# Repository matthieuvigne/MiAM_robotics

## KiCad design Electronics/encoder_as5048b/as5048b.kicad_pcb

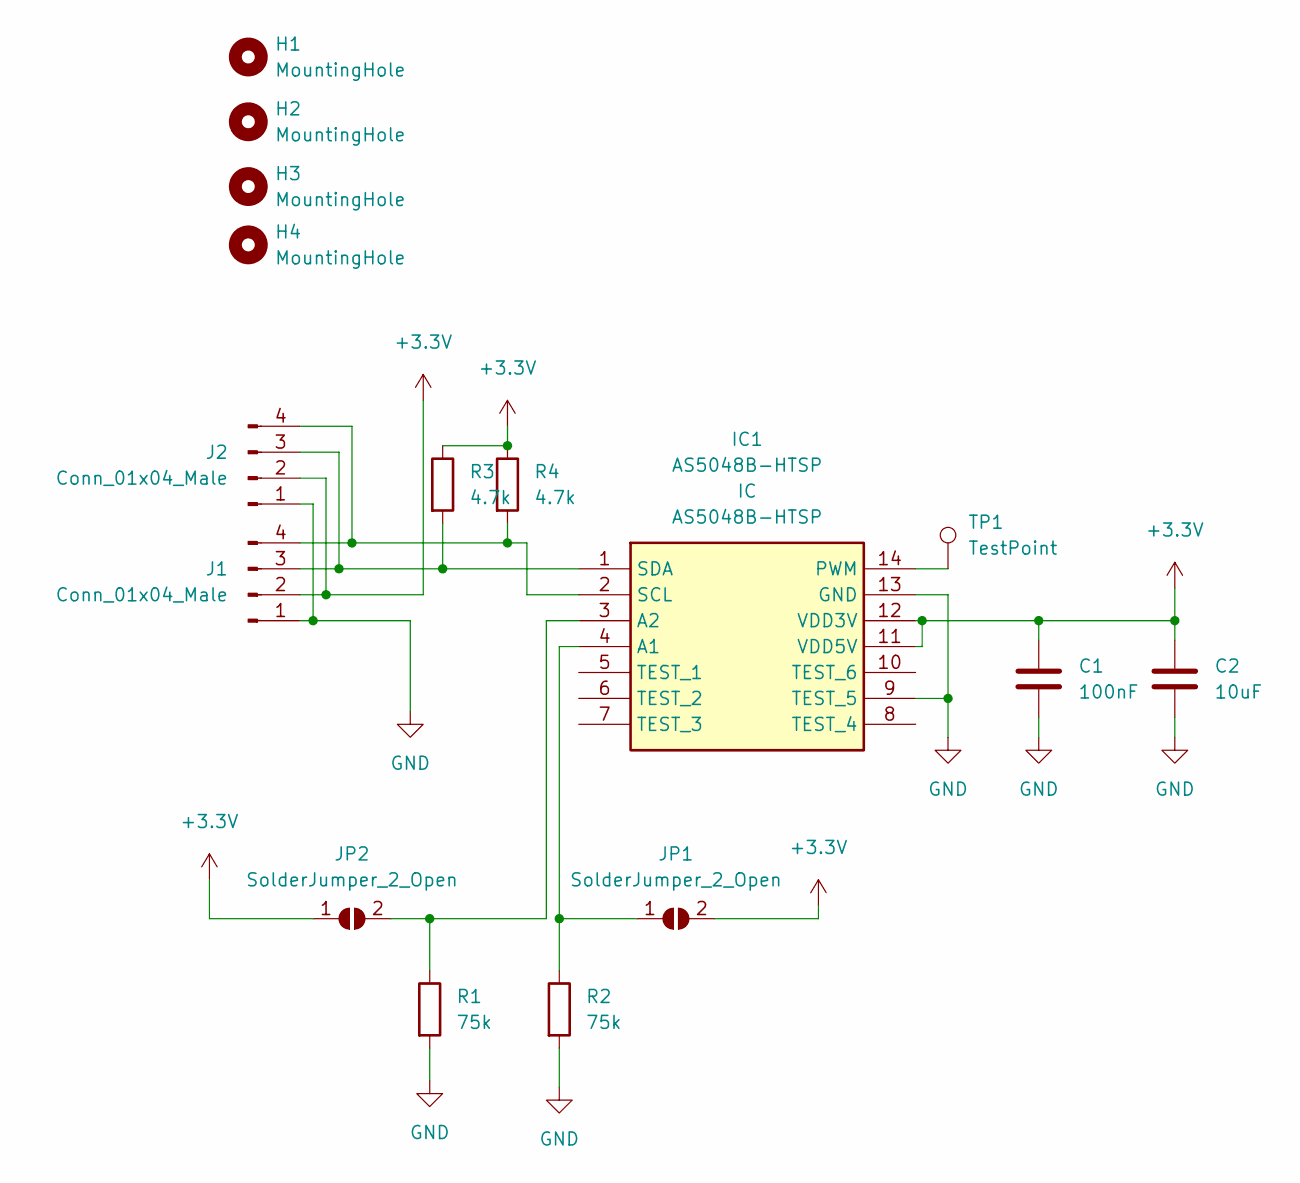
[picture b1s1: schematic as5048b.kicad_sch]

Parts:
C1: 100nF; C_0402_1005Metric_Pad0.74x0.62mm_HandSolder
C2: 10uF; C_1206_3216Metric_Pad1.33x1.80mm_HandSolder
H1, H2, H3, H4: MountingHole; MountingHole_3.2mm_M3
IC1: AS5048B-HTSP; TSSOP-14_4.4x5mm_P0.65mm; Manufacturer_Part_Number AS5048B-HTSP; Mouser Part Number 985-AS5048B-HTSP
J1, J2: Conn_01x04_Male; JST_SH_SM04B-SRSS-TB_1x04-1MP_P1.00mm_Horizontal
JP1, JP2: SolderJumper_2_Open; SolderJumper-2_P1.3mm_Open_Pad1.0x1.5mm
R1, R2: 75k; R_0805_2012Metric_Pad1.20x1.40mm_HandSolder
R3, R4: 4.7k; R_0805_2012Metric_Pad1.20x1.40mm_HandSolder
TP1: TestPoint; TestPoint_Pad_1.0x1.0mm

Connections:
+3.3V: C1.1, C2.1, IC1.11 (VDD5V), IC1.12 (VDD3V), J1.2, J2.2, JP1.2 (B), JP2.1 (A), R3.1, R4.1
GND: C1.2, C2.2, IC1.9 (TEST_5), IC1.13 (GND), J1.1, J2.1, R1.2, R2.2
unnamed: IC1.4 (A1), JP1.1 (A), R2.1
unnamed: IC1.3 (A2), JP2.2 (B), R1.1
unnamed: IC1.14 (PWM), TP1.1
unnamed: IC1.2 (SCL), J1.4, J2.4, R4.2
unnamed: IC1.1 (SDA), J1.3, J2.3, R3.2

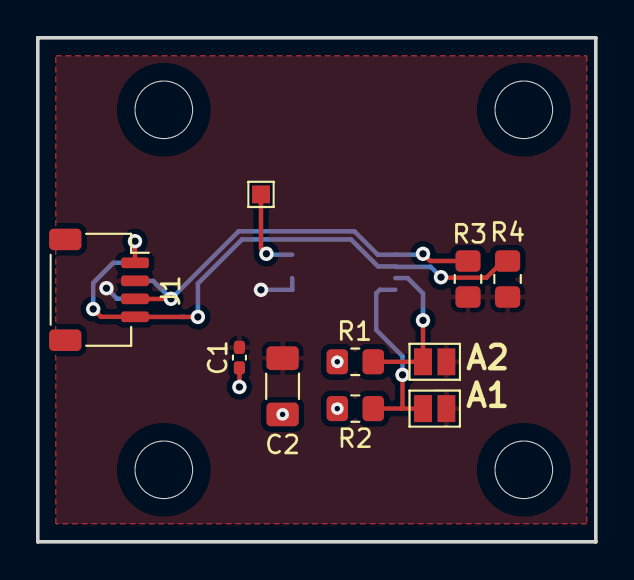
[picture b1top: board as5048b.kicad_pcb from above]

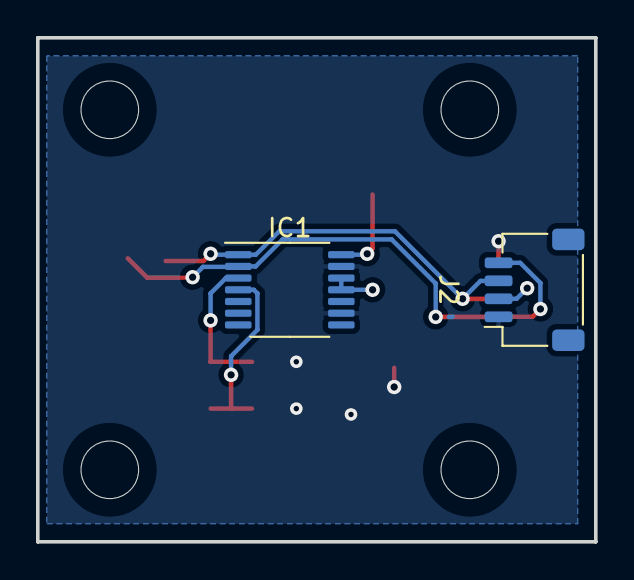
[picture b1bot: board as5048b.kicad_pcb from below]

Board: 2 copper layers, 31.0 x 28.0 mm, 16 parts (2 on the bottom side), 7 nets.

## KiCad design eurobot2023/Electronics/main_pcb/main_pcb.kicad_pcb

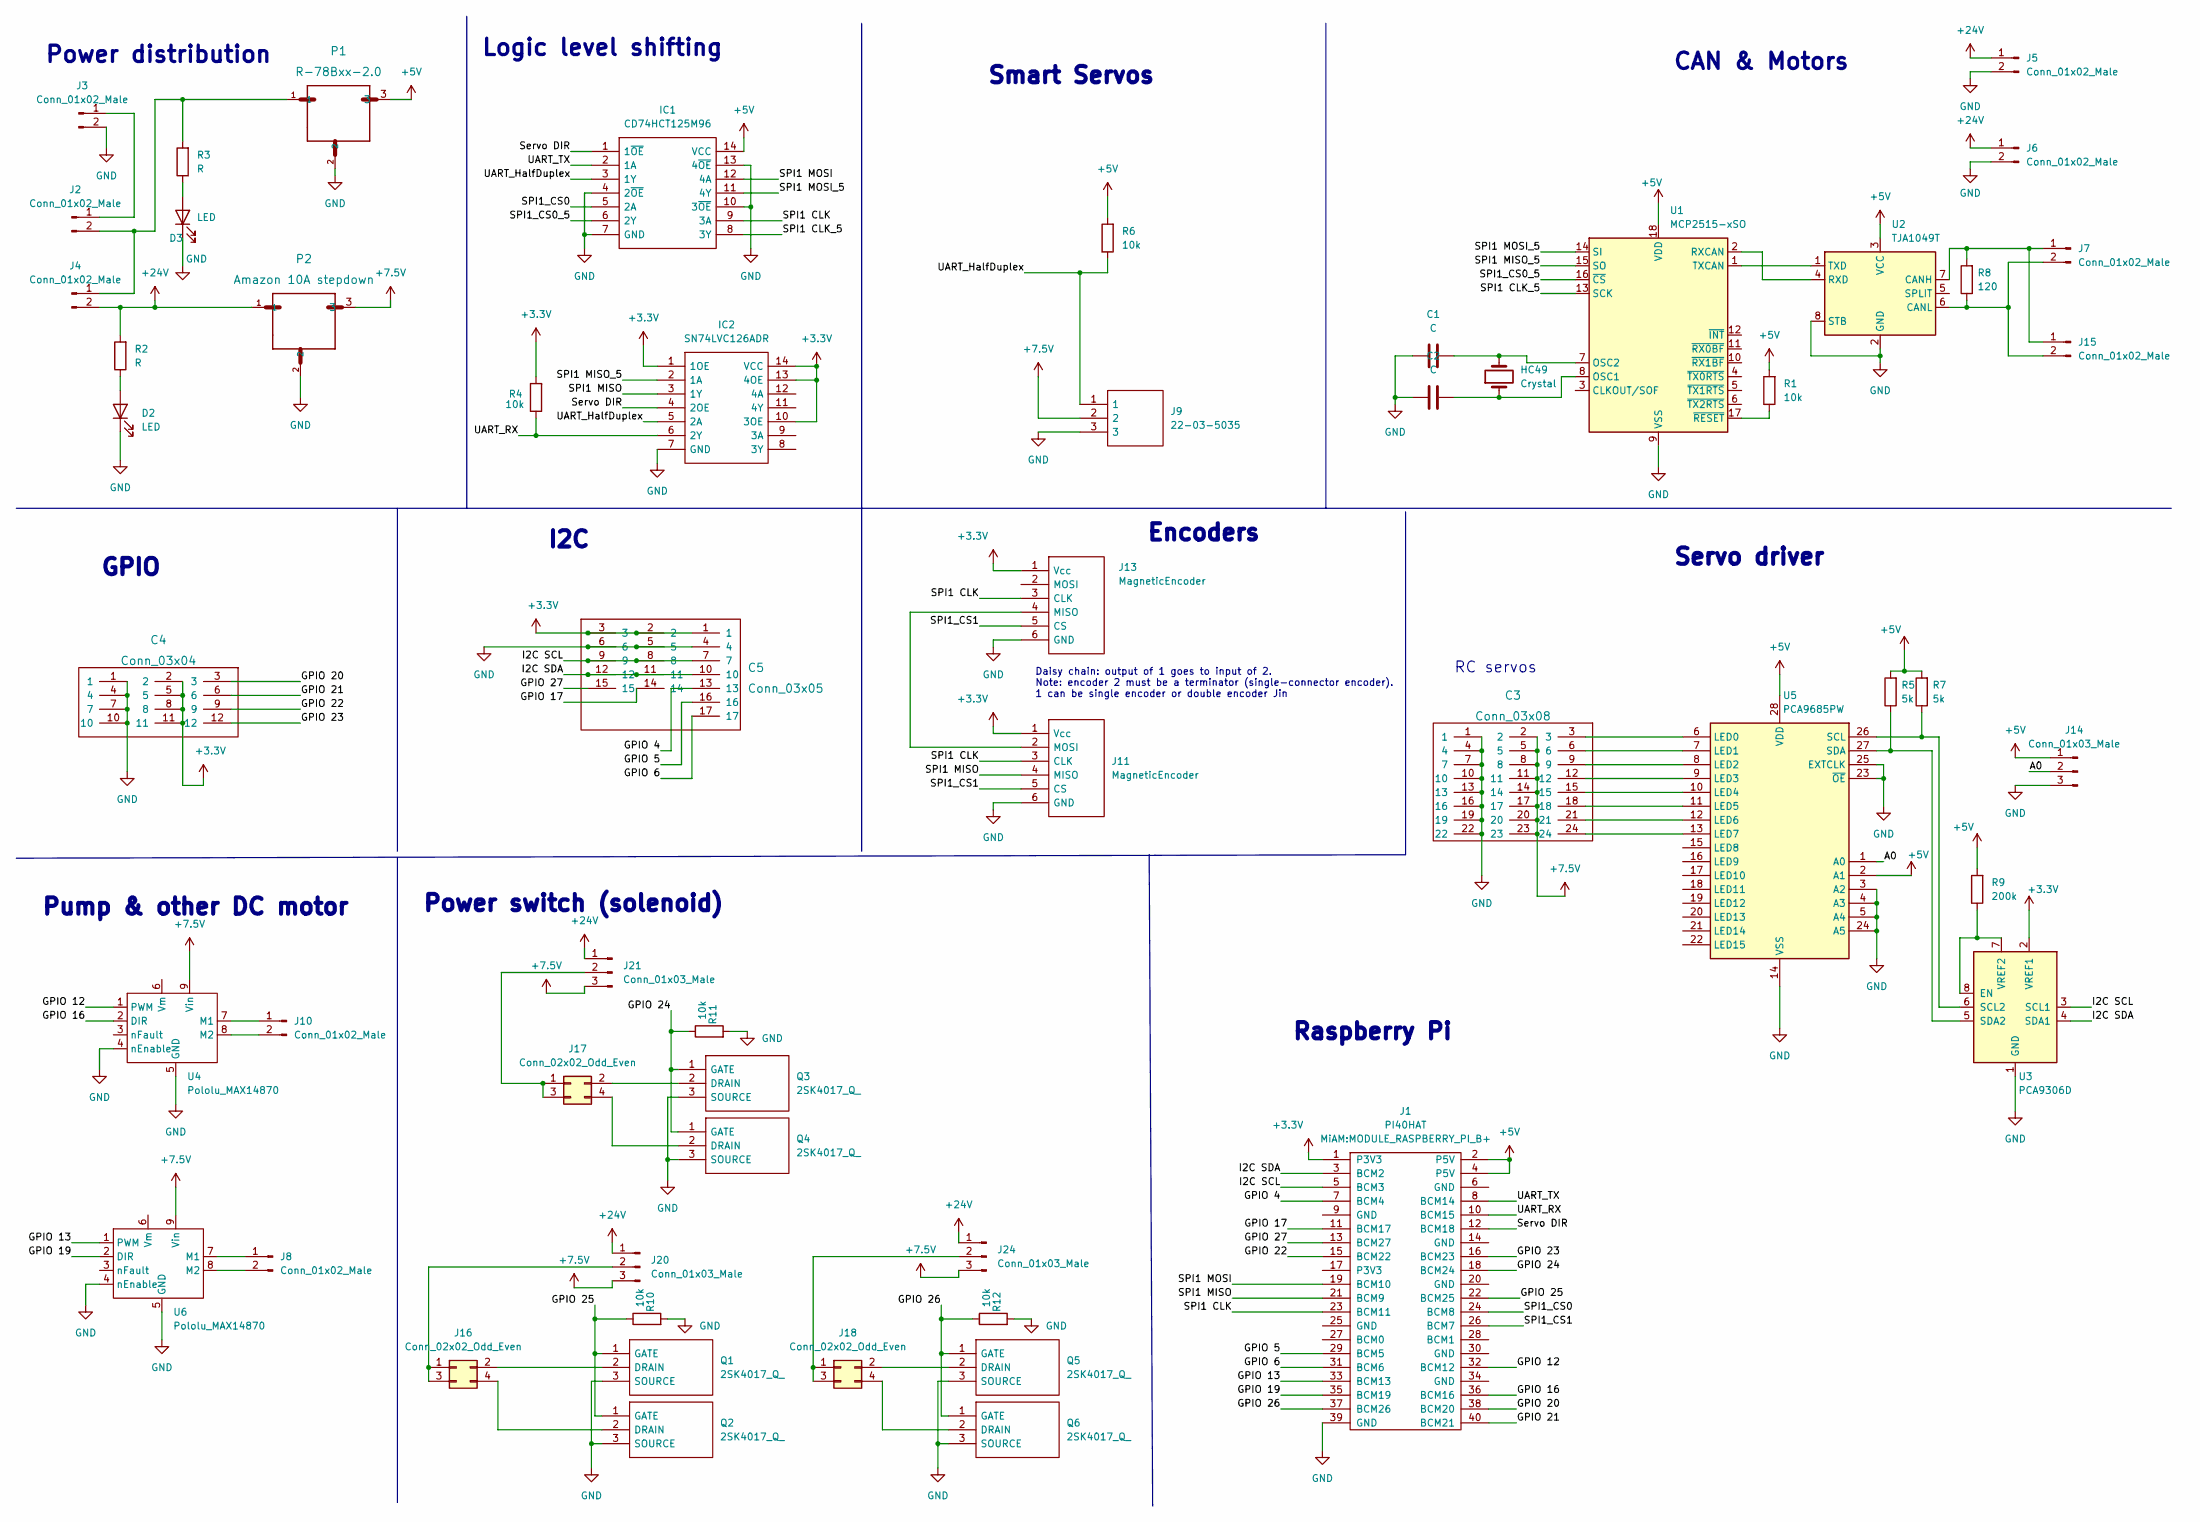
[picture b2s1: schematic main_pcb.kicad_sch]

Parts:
C1, C2: C; C_Disc_D8.0mm_W5.0mm_P10.00mm
C3: Conn_03x08; Pin_Header_Straight_3x08_Pitch2.54mm
C4: Conn_03x04; Pin_Header_Straight_3x04_Pitch2.54mm
C5: Conn_03x05; Pin_Header_Straight_3x05_Pitch2.54mm
D2, D3: LED; LED_D3.0mm
HC49: Crystal; Crystal_HC49-4H_Vertical
IC1: CD74HCT125M96; SOIC127P600X175-14N; Manufacturer_Part_Number CD74HCT125M96
IC2: SN74LVC126ADR; SOIC127P600X175-14N; Manufacturer_Part_Number SN74LVC126ADR; Mouser Part Number 595-SN74LVC126ADR
J1: PI40HAT; MODULE_RASPBERRY_PI_B+
J2, J3, J4, J5, J6: Conn_01x02_Male; XT30UM
J7, J8, J10, J15: Conn_01x02_Male; PinHeader_1x02_P2.54mm_Vertical
J9: 22-03-5035; SHDR3W60P0X250_1X3_990X490X590P; Manufacturer_Part_Number 22-03-5035
J11, J13: MagneticEncoder; 52746-0671
J14, J20, J21, J24: Conn_01x03_Male; PinHeader_1x03_P2.54mm_Vertical
J16, J17, J18: Conn_02x02_Odd_Even; PinHeader_2x02_P2.54mm_Vertical
P1: R-78Bxx-2.0; CONV_R-78Bxx-2.0
P2: Amazon 10A stepdown; StepDown10A
Q1, Q2, Q3, Q4, Q5, Q6: 2SK4017_Q_; TO230P250X650X900-3P
R1, R4, R6, R10, R11, R12: 10k; R_0805_2012Metric
R2, R3: R; R_0805_2012Metric
R5, R7: 5k; R_0805_2012Metric
R8: 120; R_0805_2012Metric
R9: 200k; R_0805_2012Metric
U1: MCP2515-xSO; SOIC-18W_7.5x11.6mm_P1.27mm
U2: TJA1049T; SOIC-8_3.9x4.9mm_P1.27mm
U3: PCA9306D; SO-8_3.9x4.9mm_P1.27mm
U4, U6: Pololu_MAX14870; PololuMAX14870
U5: PCA9685PW; TSSOP-28_4.4x9.7mm_P0.65mm

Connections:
+3.3V: C4.2, C4.5, C4.8, C4.11, C5.1, C5.2, C5.3, IC2.1 (1OE), IC2.10 (3OE), IC2.13 (4OE), IC2.14 (VCC), J1.1 (P3V3), J11.1 (Vcc), J13.1 (Vcc), R4.2, U3.2 (VREF1)
+5V: IC1.14 (VCC), J1.2 (P5V), J1.4 (P5V), J14.1, P1.3, R1.2, R5.2, R6.2, R7.2, R9.2, U1.18 (VDD), U2.3 (VCC), U5.2 (A1), U5.28 (VDD)
+7.5V: C3.2, C3.5, C3.8, C3.11, C3.14, C3.17, C3.20, C3.23, J9.2, J20.3, J21.3, J24.3, P2.3, U4.9 (Vin), U6.9 (Vin)
+24V: J4.2, J5.1, J6.1, J20.1, J21.1, J24.1, P2.1, R2.2
/A0: J14.2, U5.1 (A0)
/GPIO 4: C5.13, J1.7 (BCM4)
/GPIO 5: C5.16, J1.29 (BCM5)
/GPIO 6: C5.17, J1.31 (BCM6)
/GPIO 12: J1.32 (BCM12), U4.1 (PWM)
/GPIO 13: J1.33 (BCM13), U6.1 (PWM)
/GPIO 16: J1.36 (BCM16), U4.2 (DIR)
/GPIO 17: C5.14, J1.11 (BCM17)
/GPIO 19: J1.35 (BCM19), U6.2 (DIR)
/GPIO 20: C4.3, J1.38 (BCM20)
/GPIO 21: C4.6, J1.40 (BCM21)
/GPIO 22: C4.9, J1.15 (BCM22)
/GPIO 23: C4.12, J1.16 (BCM23)
/GPIO 24: J1.18 (BCM24), Q3.1 (GATE), Q4.1 (GATE), R11.1
/GPIO 25: J1.22 (BCM25), Q1.1 (GATE), Q2.1 (GATE), R10.1
/GPIO 26: J1.37 (BCM26), Q5.1 (GATE), Q6.1 (GATE), R12.1
/GPIO 27: C5.15, J1.13 (BCM27)
/I2C SCL: C5.7, C5.8, C5.9, J1.5 (BCM3), U3.3 (SCL1)
/I2C SDA: C5.10, C5.11, C5.12, J1.3 (BCM2), U3.4 (SDA1)
/SPI1 CLK: IC1.9 (3A), J1.23 (BCM11), J11.3 (CLK), J13.3 (CLK)
/SPI1 CLK_5: IC1.8 (3Y), U1.13 (SCK)
/SPI1 MISO: IC2.3 (1Y), J1.21 (BCM9), J11.4 (MISO)
/SPI1 MISO_5: IC2.2 (1A), U1.15 (SO)
/SPI1 MOSI: IC1.12 (4A), J1.19 (BCM10)
/SPI1 MOSI_5: IC1.11 (4Y), U1.14 (SI)
/SPI1_CS0: IC1.5 (2A), J1.24 (BCM8)
/SPI1_CS0_5: IC1.6 (2Y), U1.16 (~CS)
/SPI1_CS1: J1.26 (BCM7), J11.5 (CS), J13.5 (CS)
/Servo DIR: IC1.1 (1~OE), IC2.4 (2OE), J1.12 (BCM18)
/UART_HalfDuplex: IC1.3 (1Y), IC2.5 (2A), J9.1, R6.1
/UART_RX: IC2.6 (2Y), J1.10 (BCM15), R4.1
/UART_TX: IC1.2 (1A), J1.8 (BCM14)
GND: C1.1, C2.1, C3.1, C3.4, C3.7, C3.10, C3.13, C3.16, C3.19, C3.22, C4.1, C4.4, C4.7, C4.10, C5.4, C5.5, C5.6, D2.1 (K), D3.1 (K), IC1.4 (2~OE), IC1.7 (GND), IC1.10 (3~OE), IC1.13 (4~OE), IC2.7 (GND), J1.39 (GND), J3.2, J5.2, J6.2, J9.3, J11.6 (GND), J13.6 (GND), J14.3, P1.2, P2.2, Q1.3 (SOURCE), Q2.3 (SOURCE), Q3.3 (SOURCE), Q4.3 (SOURCE), Q5.3 (SOURCE), Q6.3 (SOURCE), R10.2, R11.2, R12.2, U1.9 (VSS), U2.2 (GND), U2.8 (STB), U3.1 (GND), U4.4 (nEnable), U4.5 (GND), U5.3 (A2), U5.4 (A3), U5.5 (A4), U5.14 (VSS), U5.23 (~OE), U5.24 (A5), U5.25 (EXTCLK), U6.4 (nEnable), U6.5 (GND)
unnamed: C1.2, HC49.2, U1.7 (OSC2)
unnamed: C2.2, HC49.1, U1.8 (OSC1)
unnamed: C3.3, U5.6 (LED0)
unnamed: C3.6, U5.7 (LED1)
unnamed: C3.9, U5.8 (LED2)
unnamed: C3.12, U5.9 (LED3)
unnamed: C3.15, U5.10 (LED4)
unnamed: C3.18, U5.11 (LED5)
unnamed: C3.21, U5.12 (LED6)
unnamed: C3.24, U5.13 (LED7)
unnamed: D2.2 (A), R2.1
unnamed: D3.2 (A), R3.1
unnamed: J2.1, J3.1
unnamed: J2.2, J4.1, P1.1, R3.2
unnamed: J8.1, U6.7 (M1)
unnamed: J8.2, U6.8 (M2)
unnamed: J10.1, U4.7 (M1)
unnamed: J10.2, U4.8 (M2)
unnamed: J11.2 (MOSI), J13.4 (MISO)
unnamed: J7.1, J15.1, R8.2, U2.7 (CANH)
unnamed: J7.2, J15.2, R8.1, U2.6 (CANL)
unnamed: J16.2, Q1.2 (DRAIN)
unnamed: J16.4, Q2.2 (DRAIN)
unnamed: J17.2, Q3.2 (DRAIN)
unnamed: J17.4, Q4.2 (DRAIN)
unnamed: J18.2, Q5.2 (DRAIN)
unnamed: J18.4, Q6.2 (DRAIN)
unnamed: J16.1, J16.3, J20.2
unnamed: J17.1, J17.3, J21.2
unnamed: J18.1, J18.3, J24.2
unnamed: R1.1, U1.17 (~RESET)
unnamed: R5.1, U3.5 (SDA2), U5.27 (SDA)
unnamed: R7.1, U3.6 (SCL2), U5.26 (SCL)
unnamed: R9.1, U3.7 (VREF2), U3.8 (EN)
unnamed: U1.1 (TXCAN), U2.1 (TXD)
unnamed: U1.2 (RXCAN), U2.4 (RXD)

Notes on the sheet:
Encoders
Power switch (solenoid)
CAN & Motors
Servo driver
GPIO
I2C
Smart Servos
Power distribution
Logic level shifting
RC servos
Pump & other DC motor
Daisy chain: output of 1 goes to input of 2. Note: encoder 2 must be a terminator (single-connector encoder). 1 can be single encoder or double encoder Jin
Raspberry Pi

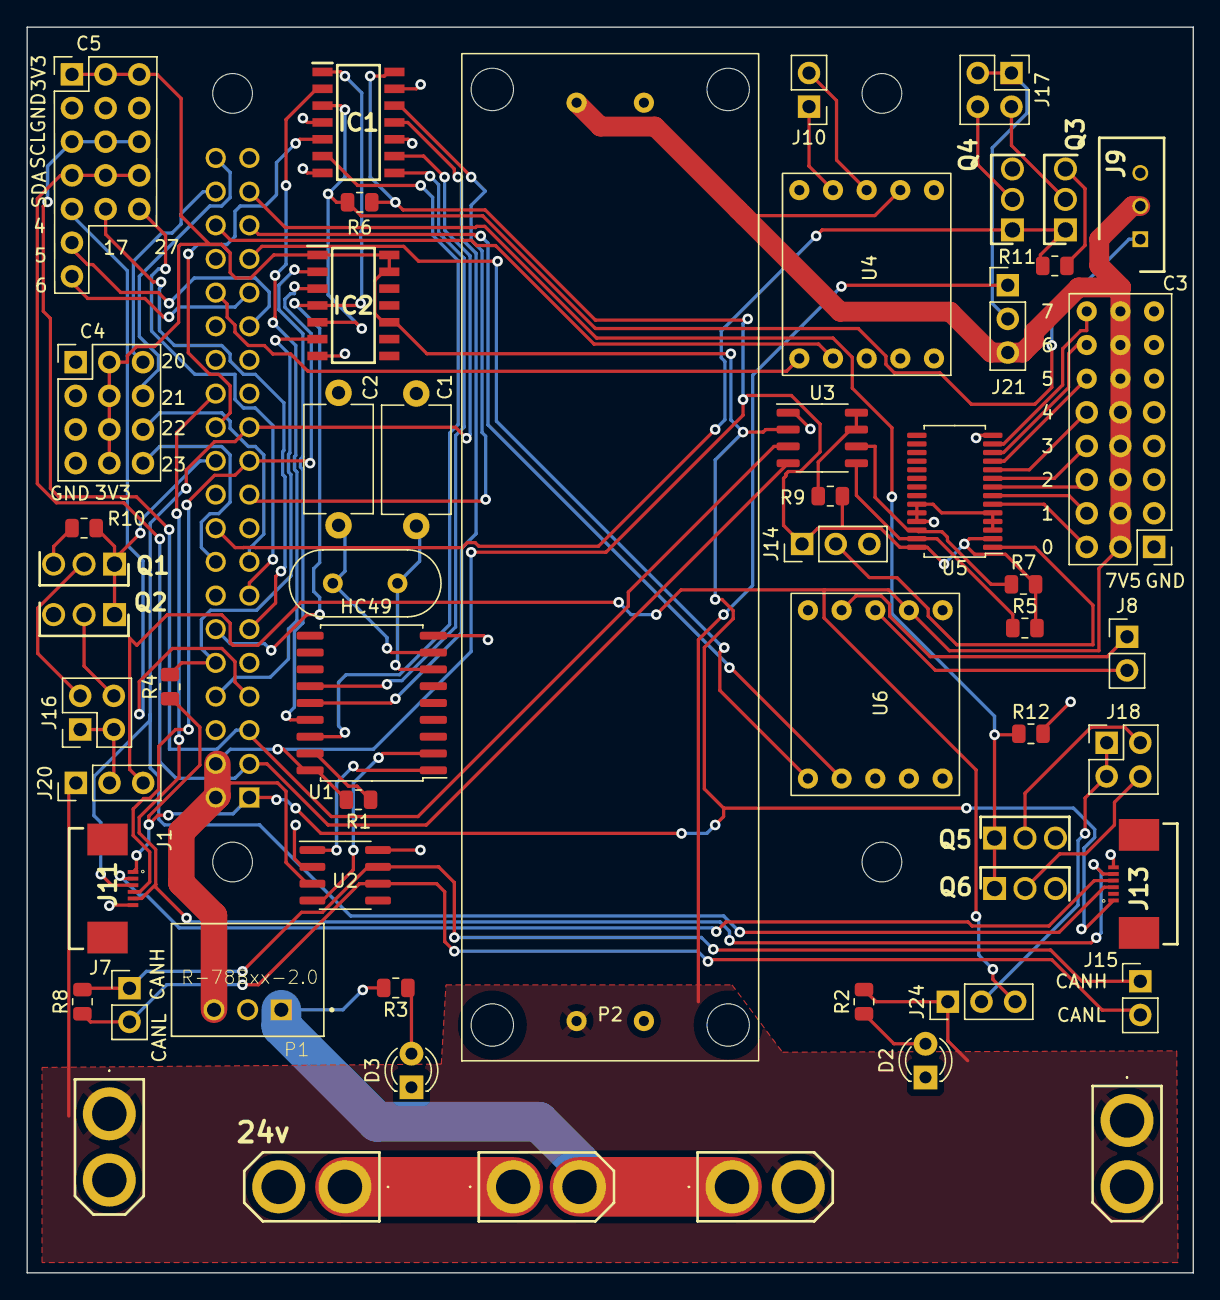
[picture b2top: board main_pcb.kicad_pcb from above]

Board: 2 copper layers, 88.0 x 94.0 mm, 56 parts (0 on the bottom side), 73 nets.

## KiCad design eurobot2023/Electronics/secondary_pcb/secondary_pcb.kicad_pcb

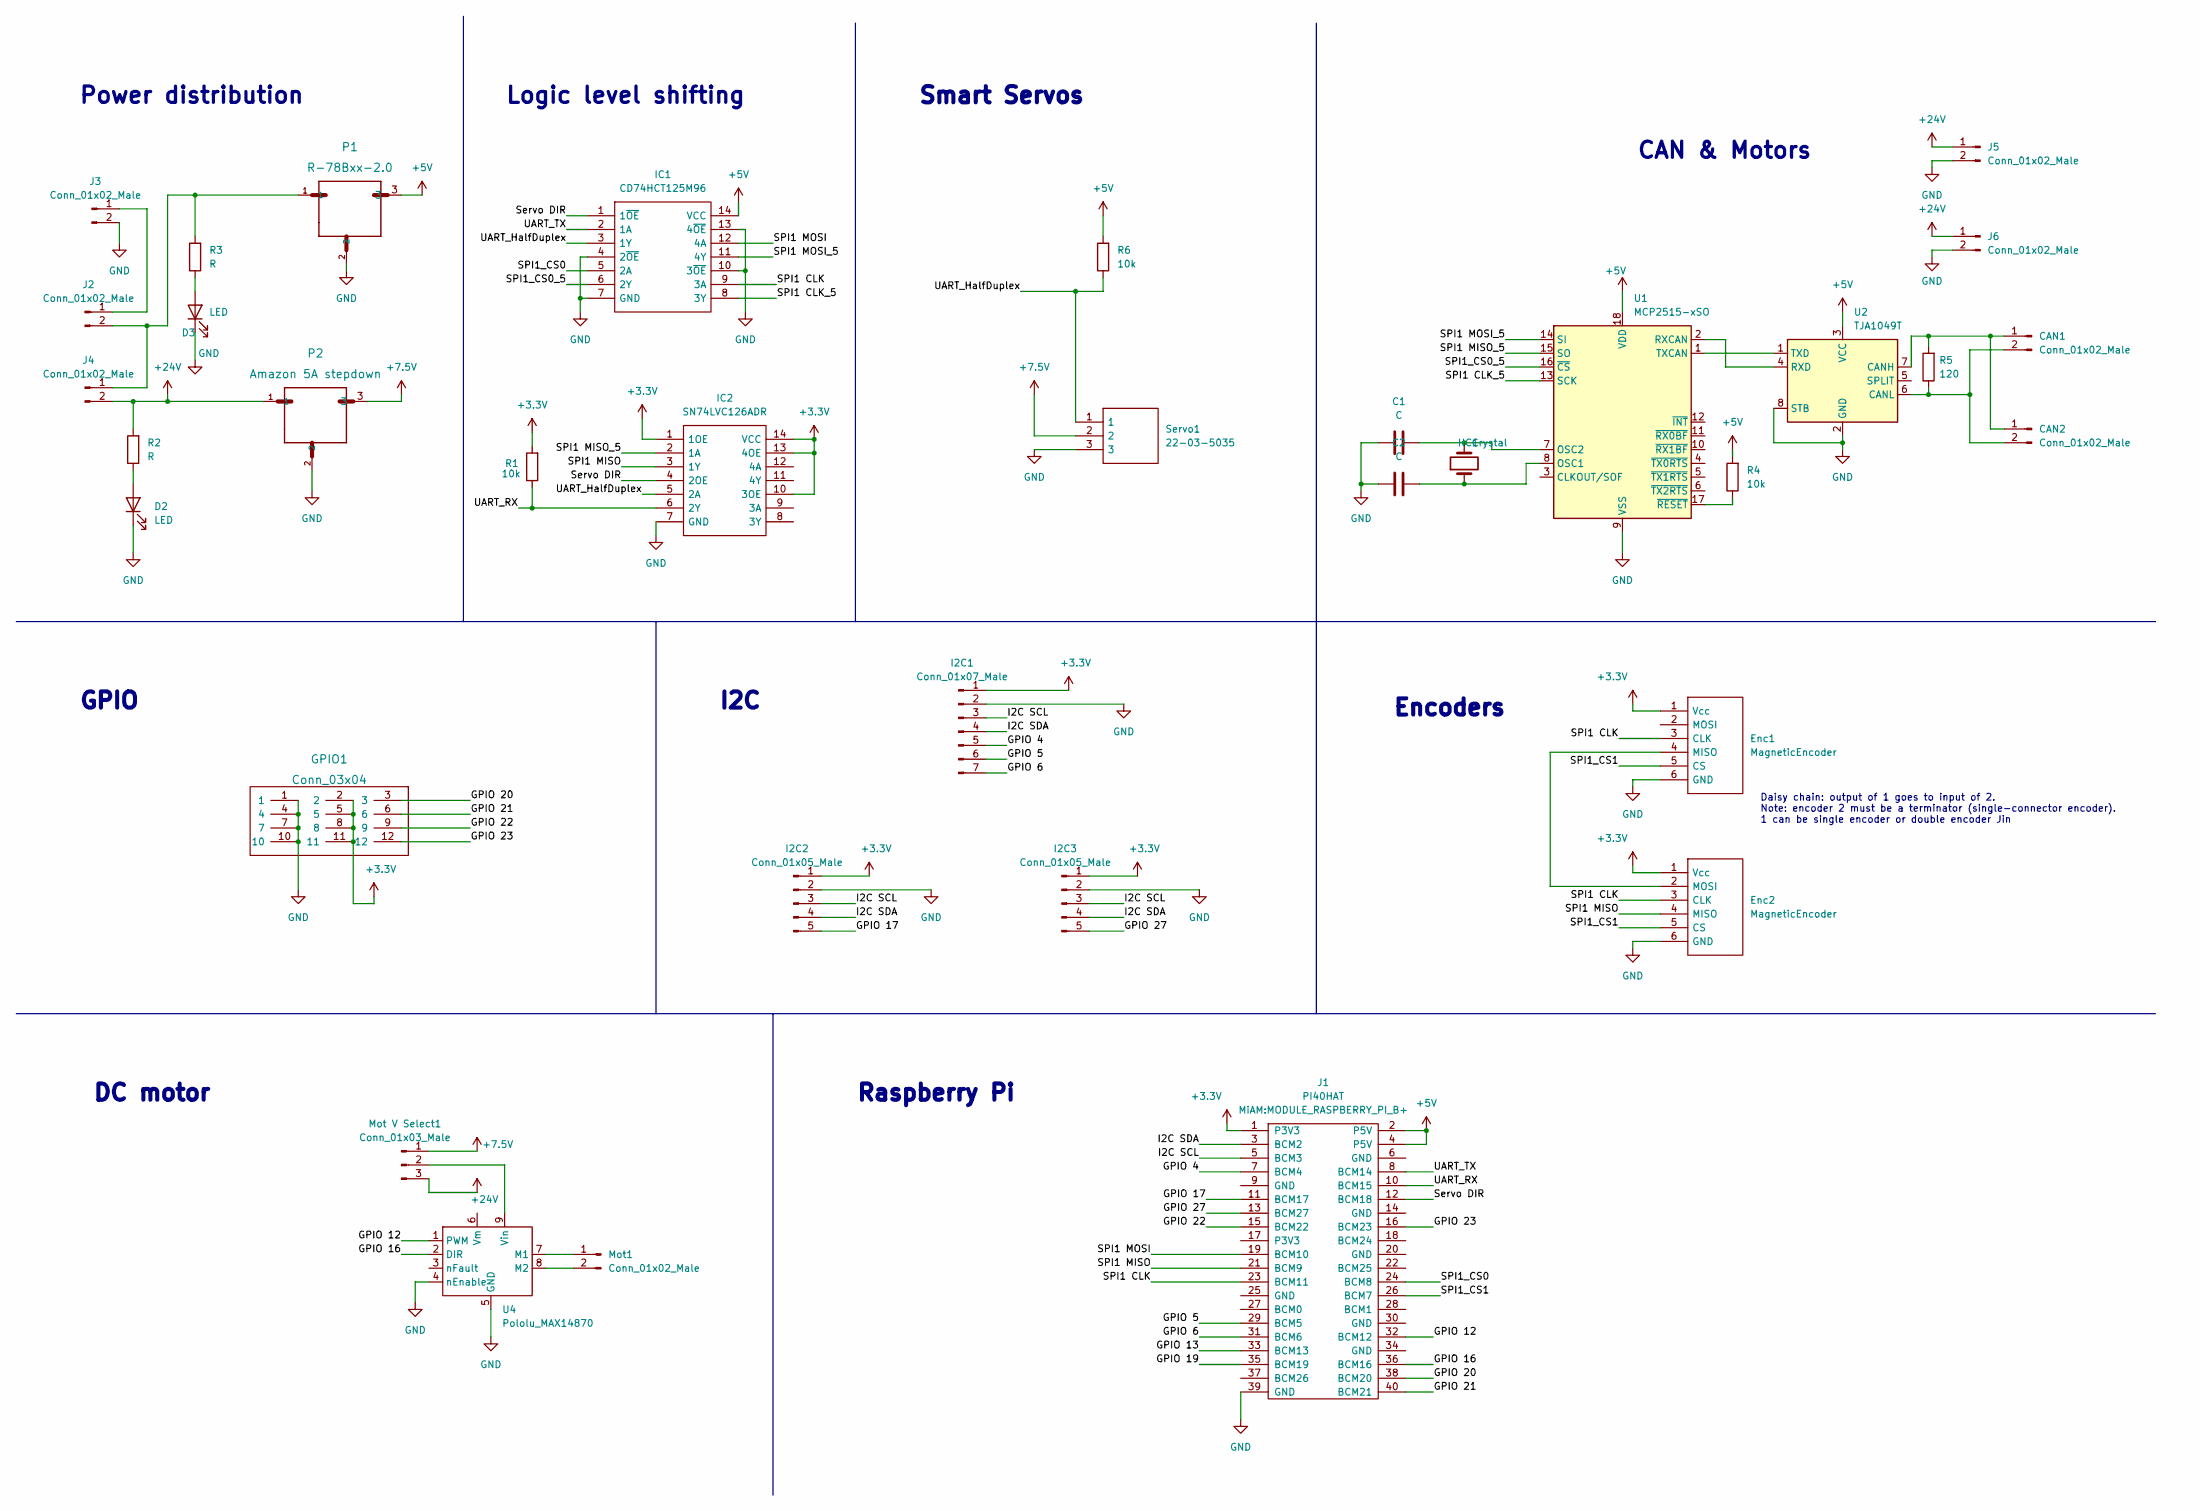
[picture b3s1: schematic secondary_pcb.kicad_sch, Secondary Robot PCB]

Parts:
C1, C2: C; C_Disc_D8.0mm_W5.0mm_P10.00mm
CAN1, CAN2: Conn_01x02_Male; PinHeader_1x02_P2.54mm_Vertical
D2, D3: LED; LED_D3.0mm
Enc1, Enc2: MagneticEncoder; 52746-0671
GPIO1: Conn_03x04; Pin_Header_Straight_3x04_Pitch2.54mm
HC1: Crystal; Crystal_HC49-4H_Vertical
I2C1: Conn_01x07_Male; PinHeader_1x07_P2.54mm_Vertical
I2C2, I2C3: Conn_01x05_Male; PinHeader_1x05_P2.54mm_Vertical
IC1: CD74HCT125M96; SOIC127P600X175-14N; Manufacturer_Part_Number CD74HCT125M96
IC2: SN74LVC126ADR; SOIC127P600X175-14N; Manufacturer_Part_Number SN74LVC126ADR; Mouser Part Number 595-SN74LVC126ADR
J1: PI40HAT; MODULE_RASPBERRY_PI_B+
J2, J3, J4, J5, J6: Conn_01x02_Male; XT30UM
Mot1: Conn_01x02_Male; PinHeader_1x02_P2.54mm_Vertical
Mot V Select1: Conn_01x03_Male; PinHeader_1x03_P2.54mm_Vertical
P1: R-78Bxx-2.0; CONV_R-78Bxx-2.0
P2: Amazon 5A stepdown; StepDown5A
R1, R4, R6: 10k; R_0805_2012Metric
R2, R3: R; R_0805_2012Metric
R5: 120; R_0805_2012Metric
Servo1: 22-03-5035; SHDR3W60P0X250_1X3_990X490X590P; Manufacturer_Part_Number 22-03-5035
U1: MCP2515-xSO; SOIC-18W_7.5x11.6mm_P1.27mm
U2: TJA1049T; SOIC-8_3.9x4.9mm_P1.27mm
U4: Pololu_MAX14870; PololuMAX14870

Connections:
+3.3V: Enc1.1 (Vcc), Enc2.1 (Vcc), GPIO1.2, GPIO1.5, GPIO1.8, GPIO1.11, I2C1.1, I2C2.1, I2C3.1, IC2.1 (1OE), IC2.10 (3OE), IC2.13 (4OE), IC2.14 (VCC), J1.1 (P3V3), R1.2
+5V: IC1.14 (VCC), J1.2 (P5V), J1.4 (P5V), P1.3, R4.2, R6.2, U1.18 (VDD), U2.3 (VCC)
+7.5V: Mot V Select1.1, P2.3, Servo1.2
+24V: J4.2, J5.1, J6.1, Mot V Select1.3, P2.1, R2.2
/GPIO 4: I2C1.5, J1.7 (BCM4)
/GPIO 5: I2C1.6, J1.29 (BCM5)
/GPIO 6: I2C1.7, J1.31 (BCM6)
/GPIO 12: J1.32 (BCM12), U4.1 (PWM)
/GPIO 16: J1.36 (BCM16), U4.2 (DIR)
/GPIO 17: I2C2.5, J1.11 (BCM17)
/GPIO 20: GPIO1.3, J1.38 (BCM20)
/GPIO 21: GPIO1.6, J1.40 (BCM21)
/GPIO 22: GPIO1.9, J1.15 (BCM22)
/GPIO 23: GPIO1.12, J1.16 (BCM23)
/GPIO 27: I2C3.5, J1.13 (BCM27)
/I2C SCL: I2C1.3, I2C2.3, I2C3.3, J1.5 (BCM3)
/I2C SDA: I2C1.4, I2C2.4, I2C3.4, J1.3 (BCM2)
/SPI1 CLK: Enc1.3 (CLK), Enc2.3 (CLK), IC1.9 (3A), J1.23 (BCM11)
/SPI1 CLK_5: IC1.8 (3Y), U1.13 (SCK)
/SPI1 MISO: Enc2.4 (MISO), IC2.3 (1Y), J1.21 (BCM9)
/SPI1 MISO_5: IC2.2 (1A), U1.15 (SO)
/SPI1 MOSI: IC1.12 (4A), J1.19 (BCM10)
/SPI1 MOSI_5: IC1.11 (4Y), U1.14 (SI)
/SPI1_CS0: IC1.5 (2A), J1.24 (BCM8)
/SPI1_CS0_5: IC1.6 (2Y), U1.16 (~CS)
/SPI1_CS1: Enc1.5 (CS), Enc2.5 (CS), J1.26 (BCM7)
/Servo DIR: IC1.1 (1~OE), IC2.4 (2OE), J1.12 (BCM18)
/UART_HalfDuplex: IC1.3 (1Y), IC2.5 (2A), R6.1, Servo1.1
/UART_RX: IC2.6 (2Y), J1.10 (BCM15), R1.1
/UART_TX: IC1.2 (1A), J1.8 (BCM14)
GND: C1.1, C2.1, D2.1 (K), D3.1 (K), Enc1.6 (GND), Enc2.6 (GND), GPIO1.1, GPIO1.4, GPIO1.7, GPIO1.10, I2C1.2, I2C2.2, I2C3.2, IC1.4 (2~OE), IC1.7 (GND), IC1.10 (3~OE), IC1.13 (4~OE), IC2.7 (GND), J1.39 (GND), J3.2, J5.2, J6.2, P1.2, P2.2, Servo1.3, U1.9 (VSS), U2.2 (GND), U2.8 (STB), U4.4 (nEnable), U4.5 (GND)
unnamed: C1.2, HC1.2, U1.7 (OSC2)
unnamed: C2.2, HC1.1, U1.8 (OSC1)
unnamed: CAN1.1, CAN2.1, R5.2, U2.7 (CANH)
unnamed: CAN1.2, CAN2.2, R5.1, U2.6 (CANL)
unnamed: D2.2 (A), R2.1
unnamed: D3.2 (A), R3.1
unnamed: Enc1.4 (MISO), Enc2.2 (MOSI)
unnamed: J2.1, J3.1
unnamed: J2.2, J4.1, P1.1, R3.2
unnamed: Mot1.1, U4.7 (M1)
unnamed: Mot1.2, U4.8 (M2)
unnamed: Mot V Select1.2, U4.9 (Vin)
unnamed: R4.1, U1.17 (~RESET)
unnamed: U1.1 (TXCAN), U2.1 (TXD)
unnamed: U1.2 (RXCAN), U2.4 (RXD)

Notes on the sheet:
Encoders
Raspberry Pi
GPIO
I2C
Smart Servos
Power distribution
Logic level shifting
DC motor
Daisy chain: output of 1 goes to input of 2. Note: encoder 2 must be a terminator (single-connector encoder). 1 can be single encoder or double encoder Jin
CAN & Motors

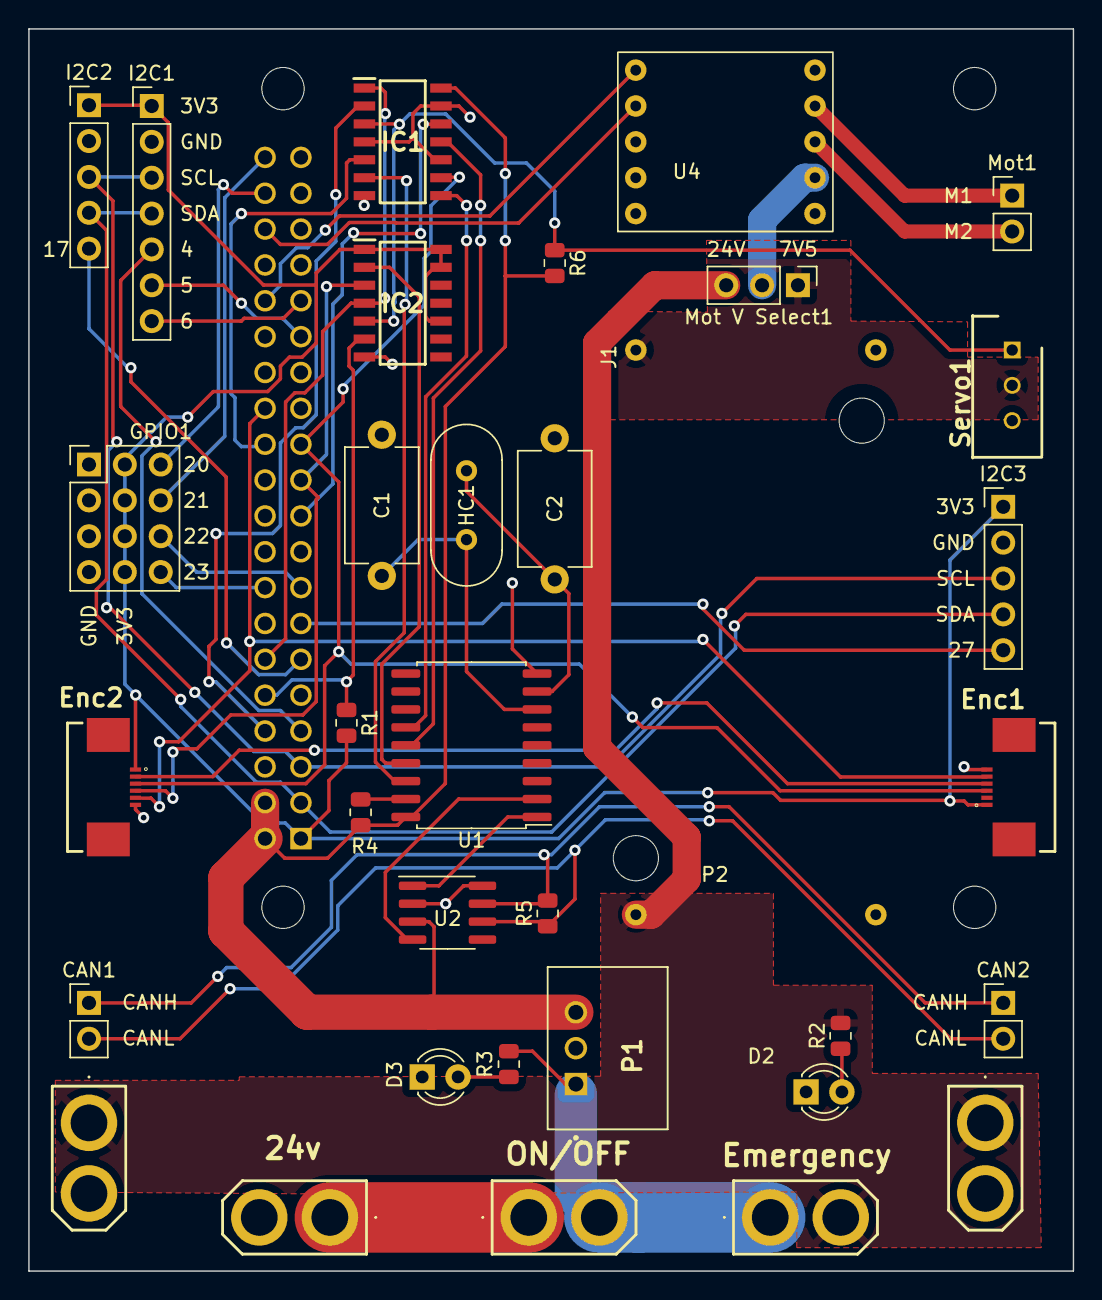
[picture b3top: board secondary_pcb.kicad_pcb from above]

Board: 2 copper layers, 74.0 x 88.0 mm, 35 parts (0 on the bottom side), 46 nets.
